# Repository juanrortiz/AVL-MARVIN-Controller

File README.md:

# MARVIN Embedded Controller — Electronics Hardware Design

**CPP AVL | Fall Cohort 2026 | Intelligent Ground Vehicle Competition (IGVC)**

This repository contains the hardware design files and embedded firmware source for a custom controller developed for **MARVIN**, the CPP Autonomous Vehicle Lab (AVL) competition platform.

The controller is built around the **STM32F767ZIT6** microcontroller and is intended to modernize MARVIN's motor-control electronics, replacing the existing **Teensy 4.1**-based controller with an STM32-based system.

## Project Goals

During the Fall 2026 cohort, the Electronics Hardware Design Team aims to:

- Design and integrate a new STM32-based embedded control system for MARVIN.
- Migrate CAN-based motor control from the existing Teensy 4.1 controller.
- Support the currently used **SPARK MAX** motor drivers over CAN.
- Improve compatibility with future **ODrive S Series** CAN motor drivers.
- Standardize the control hardware around an industry-common STM32 platform.
- Validate reliable communication, power monitoring, and operation on the vehicle.

## Hardware Overview

The custom controller integrates the following components and subsystems:

| Subsystem | Description |
| --- | --- |
| Main MCU | STM32F767ZIT6 |
| CAN Interface | CAN transceiver for communication with motor drivers |
| USB / Serial | Serial-to-USB interface for communication and debugging |
| Power Monitoring | Onboard power-monitoring circuitry |
| PCB Design | KiCad schematic and PCB layout files |

> **Note:** Electrical specifications, connector pinouts, CAN configuration, and power limits should be verified against the latest KiCad design before hardware is assembled or connected.

## Repository Contents

This repository includes:

- **KiCad project files** — schematics, PCB layouts, and related hardware design assets.
- **Firmware source code** — embedded application code targeting the STM32F767ZIT6.
- **Makefile** — firmware build configuration.
- **Linker scripts** — memory layout and linking configuration for the STM32 target.

The exact directory layout may evolve as the project develops.

## Firmware Dependencies

The firmware depends on official **STMicroelectronics STM32 HAL and CMSIS libraries**. These libraries are **not necessarily bundled with this repository** and must be obtained separately from the official STM32 software packages.

Recommended sources:

- [STM32CubeF7 firmware package](https://github.com/STMicroelectronics/STM32CubeF7)
- [STM32F7 HAL drivers](https://github.com/STMicroelectronics/stm32f7xx-hal-driver)
- [STM32Cube ecosystem](https://www.st.com/en/embedded-software/stm32cube-mcu-mpu-packages.html)

Ensure the HAL, CMSIS, startup files, include paths, and linker configuration match the **STM32F767ZIT6** and the project's Makefile. Dependency setup and build commands will be documented as the firmware structure is finalized.

## Development Roadmap

- [ ] Finalize and review the KiCad schematic and PCB design.
- [ ] Assemble and bring up the STM32F767ZIT6 controller hardware.
- [ ] Configure the clock tree, GPIO, CAN, serial/USB, and power-monitoring peripherals.
- [ ] Integrate official STM32 HAL/CMSIS dependencies into the firmware build.
- [ ] Implement and validate CAN communication with SPARK MAX motor drivers.
- [ ] Migrate motor-control functionality from Teensy 4.1 to STM32.
- [ ] Evaluate and implement compatibility with ODrive S Series CAN motor drivers.
- [ ] Perform bench testing, vehicle integration, and system validation.

*Checklist items represent project objectives, not confirmed implementation status.*

## Development and Testing Notes

Before connecting motor drivers or installing the controller on MARVIN:

1. Verify PCB power rails, grounding, and connector pinouts.
2. Confirm CAN bus voltage levels, termination, bitrate, and device-specific message protocols.
3. Test communication and power monitoring on the bench before enabling motor outputs.
4. Validate fault handling and emergency-stop behavior as part of vehicle integration.

**Important:** SPARK MAX and ODrive motor controllers may use different CAN protocols. Electrical CAN compatibility alone does not guarantee firmware-level interoperability; each device requires the appropriate protocol implementation.

## Team

**CPP Autonomous Vehicle Lab (AVL)**  
**Fall Cohort 2026 — MARVIN Electronics Hardware Design Team**  
**Competition:** Intelligent Ground Vehicle Competition (IGVC)

## Project Status

**In development — Fall 2026 cohort.** Hardware, firmware, and integration details are subject to change as the controller is developed and validated.

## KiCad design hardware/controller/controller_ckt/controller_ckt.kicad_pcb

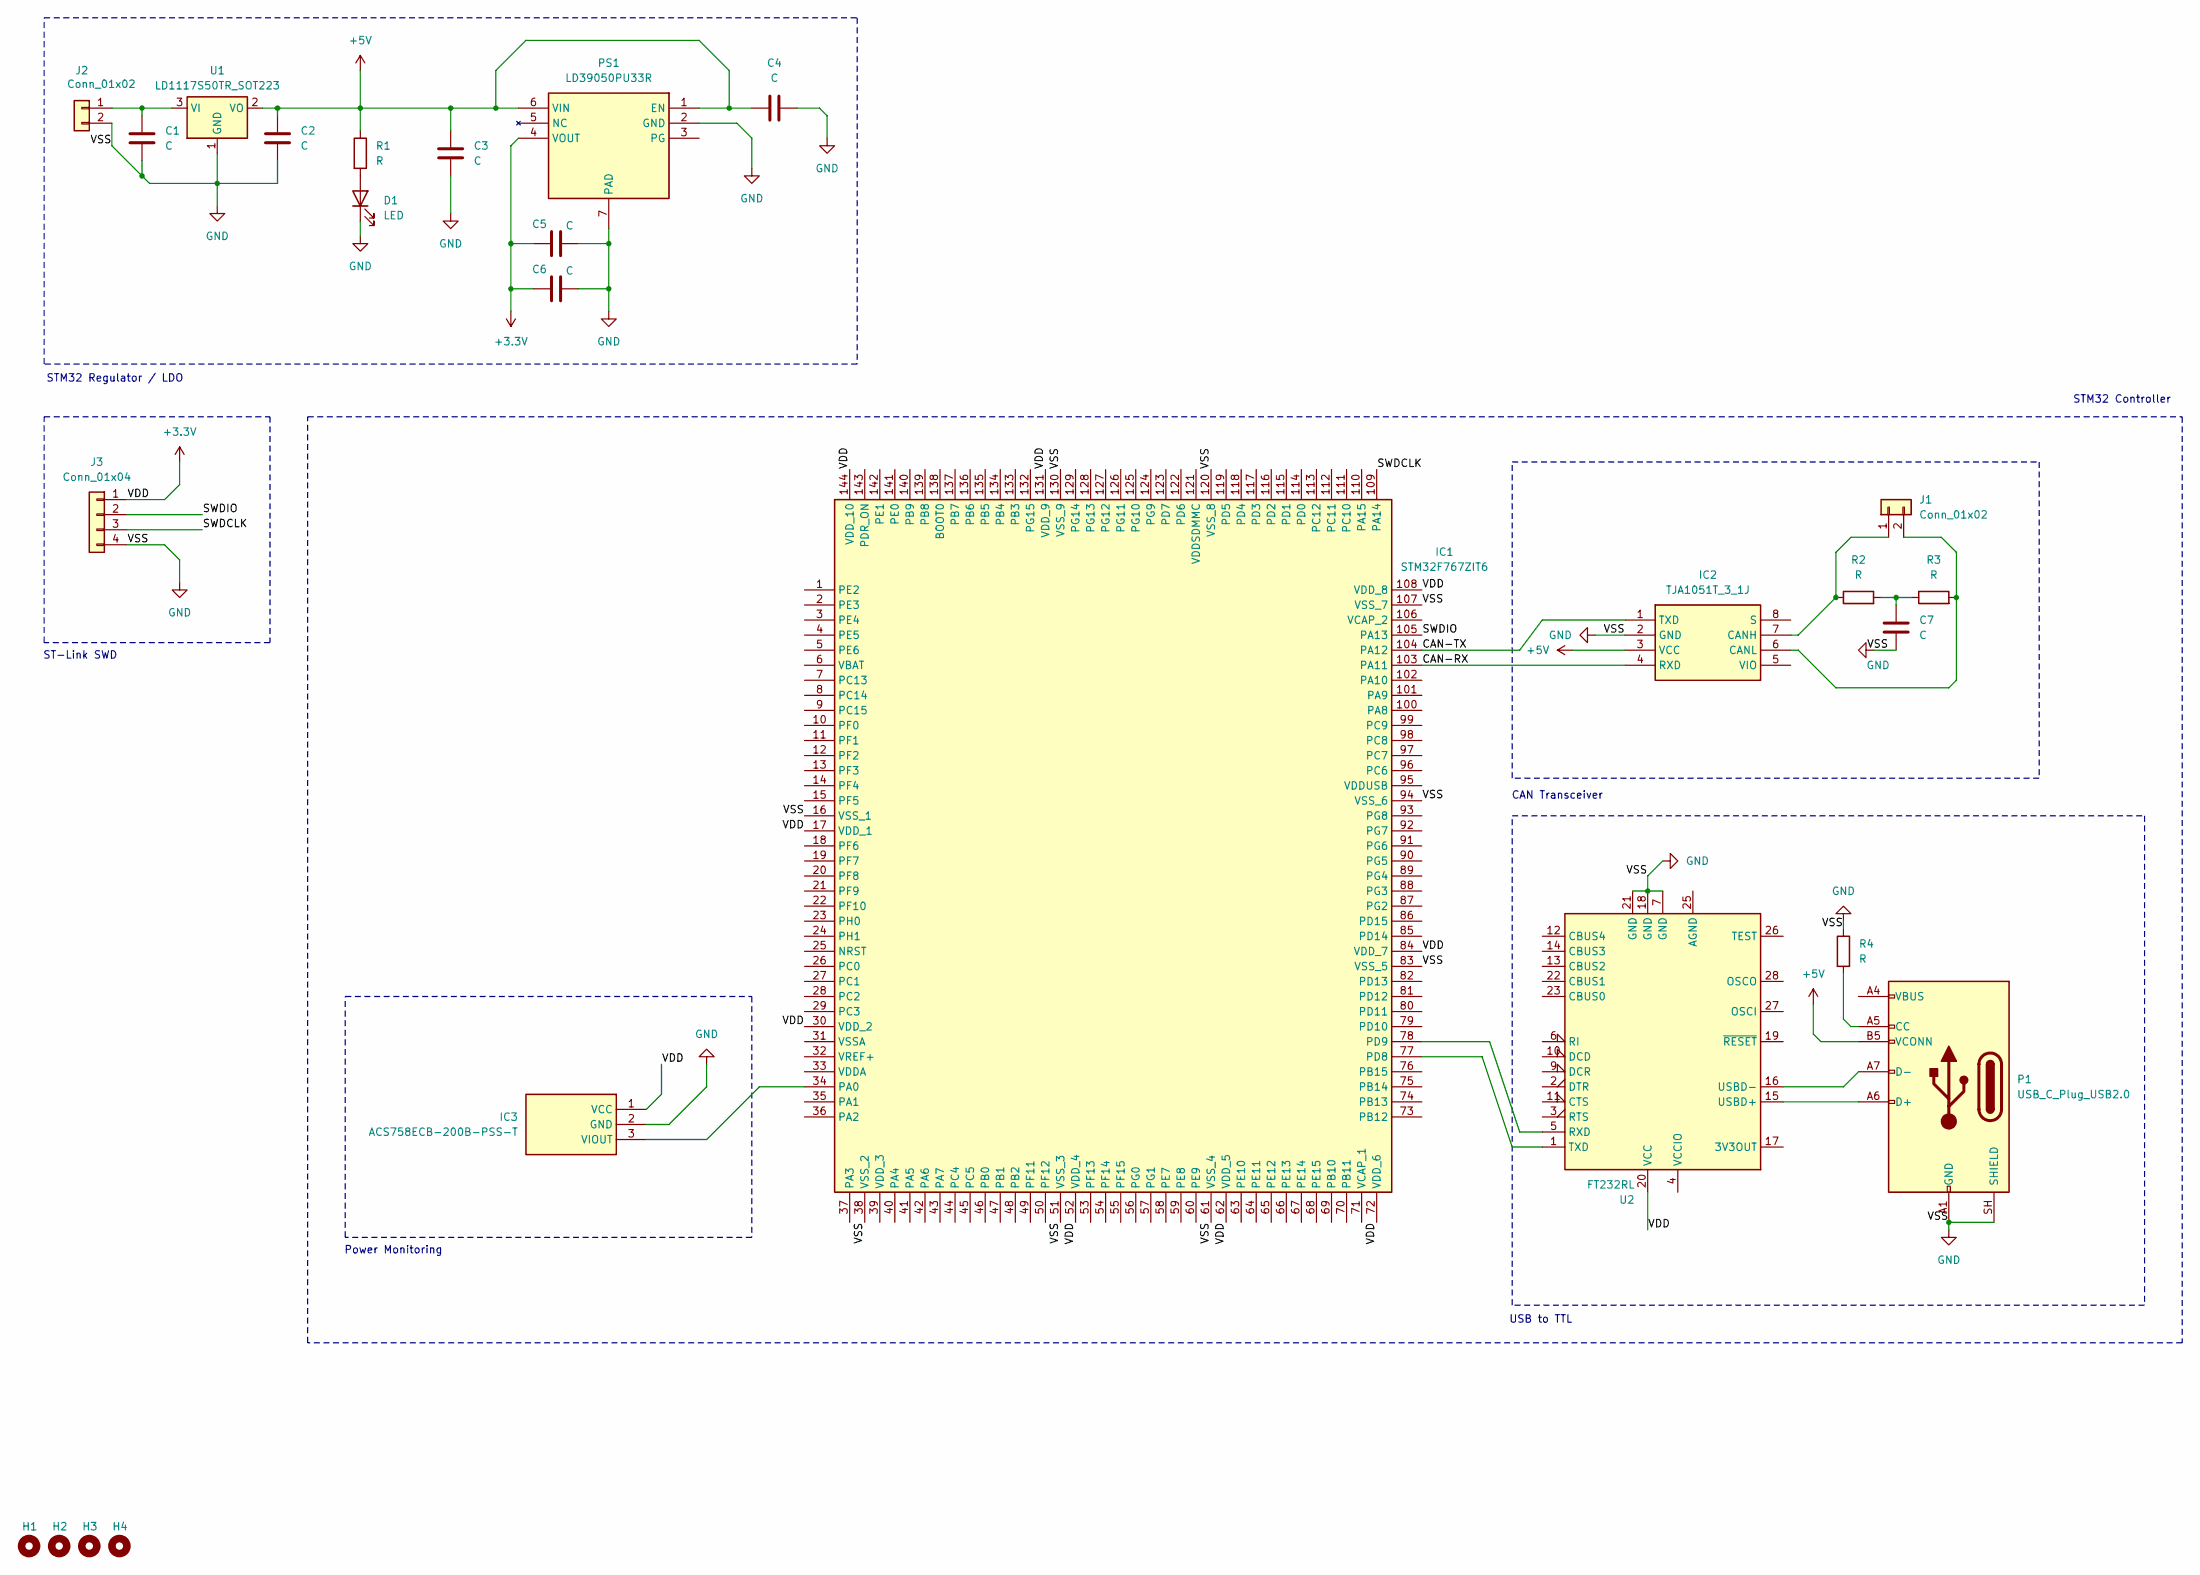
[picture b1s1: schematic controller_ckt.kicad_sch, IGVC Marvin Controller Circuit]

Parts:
C1, C2, C3, C4, C5, C6, C7: C; C_0805_2012Metric
D1: LED; LED_0805_2012Metric
H1, H2, H3, H4: MountingHole_3.2mm_M3
IC1: STM32F767ZIT6; QFP50P2200X2200X160-144N; Mouser Part Number 511-STM32F767ZIT6
IC2: TJA1051T_3_1J; SOIC127P600X175-8N; Mouser Part Number 771-TJA1051T/3/1J
IC3: ACS758ECB-200B-PSS-T; ACS758ECB200BPSST; Mouser Part Number 250-758ECB200BPSST
J1, J2: Conn_01x02; TerminalBlock_Phoenix_MKDS-3-2-5.08_1x02_P5.08mm_Horizontal
J3: Conn_01x04; PinHeader_1x04_P2.54mm_Vertical
P1: USB_C_Plug_USB2.0; USB_C_Receptacle_HCTL_HC-TYPE-C-16P-01A
PS1: LD39050PU33R; SON95P300X300X100-7N-D; Mouser Part Number 511-LD39050PU33R
R1, R2, R3, R4: R; R_0805_2012Metric
U1: LD1117S50TR_SOT223; SOT-223-3_TabPin2
U2: FT232RL; SSOP-28_5.3x10.2mm_P0.65mm

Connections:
+3.3V: C5.1, C6.1, IC1.17 (VDD_1), IC1.30 (VDD_2), IC1.52 (VDD_4), IC1.62 (VDD_5), IC1.72 (VDD_6), IC1.84 (VDD_7), IC1.108 (VDD_8), IC1.131 (VDD_9), IC1.144 (VDD_10), IC3.1 (VCC), J3.1, PS1.4 (VOUT), U2.20 (VCC)
+5V: C2.1, C3.1, C4.1, IC2.3 (VCC), P1.B5 (VCONN), PS1.1 (EN), PS1.6 (VIN), R1.1, U1.2 (VO)
/CAN-RX: IC1.103 (PA11), IC2.4 (RXD)
/CAN-TX: IC1.104 (PA12), IC2.1 (TXD)
/SWDCLK: IC1.109 (PA14), J3.3
/SWDIO: IC1.105 (PA13), J3.2
GND: C1.2, C2.2, C3.2, C4.2, C5.2, C6.2, C7.2, D1.1 (K), IC1.16 (VSS_1), IC1.38 (VSS_2), IC1.51 (VSS_3), IC1.61 (VSS_4), IC1.83 (VSS_5), IC1.94 (VSS_6), IC1.107 (VSS_7), IC1.120 (VSS_8), IC1.130 (VSS_9), IC2.2 (GND), IC3.2 (GND), J2.2, J3.4, P1.A1 (GND), P1.A12 (GND), P1.B1 (GND), P1.B12 (GND), P1.SH (SHIELD), PS1.2 (GND), PS1.7 (PAD), R4.1, U1.1 (GND), U2.7 (GND), U2.18 (GND), U2.21 (GND)
unnamed: C7.1, R2.2, R3.1
unnamed: D1.2 (A), R1.2
unnamed: IC1.34 (PA0), IC3.3 (VIOUT)
unnamed: IC1.77 (PD8), U2.1 (TXD)
unnamed: IC1.78 (PD9), U2.5 (RXD)
unnamed: IC2.7 (CANH), J1.1, R2.1
unnamed: IC2.6 (CANL), J1.2, R3.2
unnamed: C1.1, J2.1, U1.3 (VI)
unnamed: P1.A5 (CC), R4.2
unnamed: P1.A6 (D+), U2.15 (USBD+)
unnamed: P1.A7 (D-), U2.16 (USBD-)
unnamed: P1.A4 (VBUS), P1.A9 (VBUS), P1.B4 (VBUS), P1.B9 (VBUS)

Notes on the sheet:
STM32 Regulator / LDO
USB to TTL
Power Monitoring
STM32 Controller
ST-Link SWD
CAN Transceiver

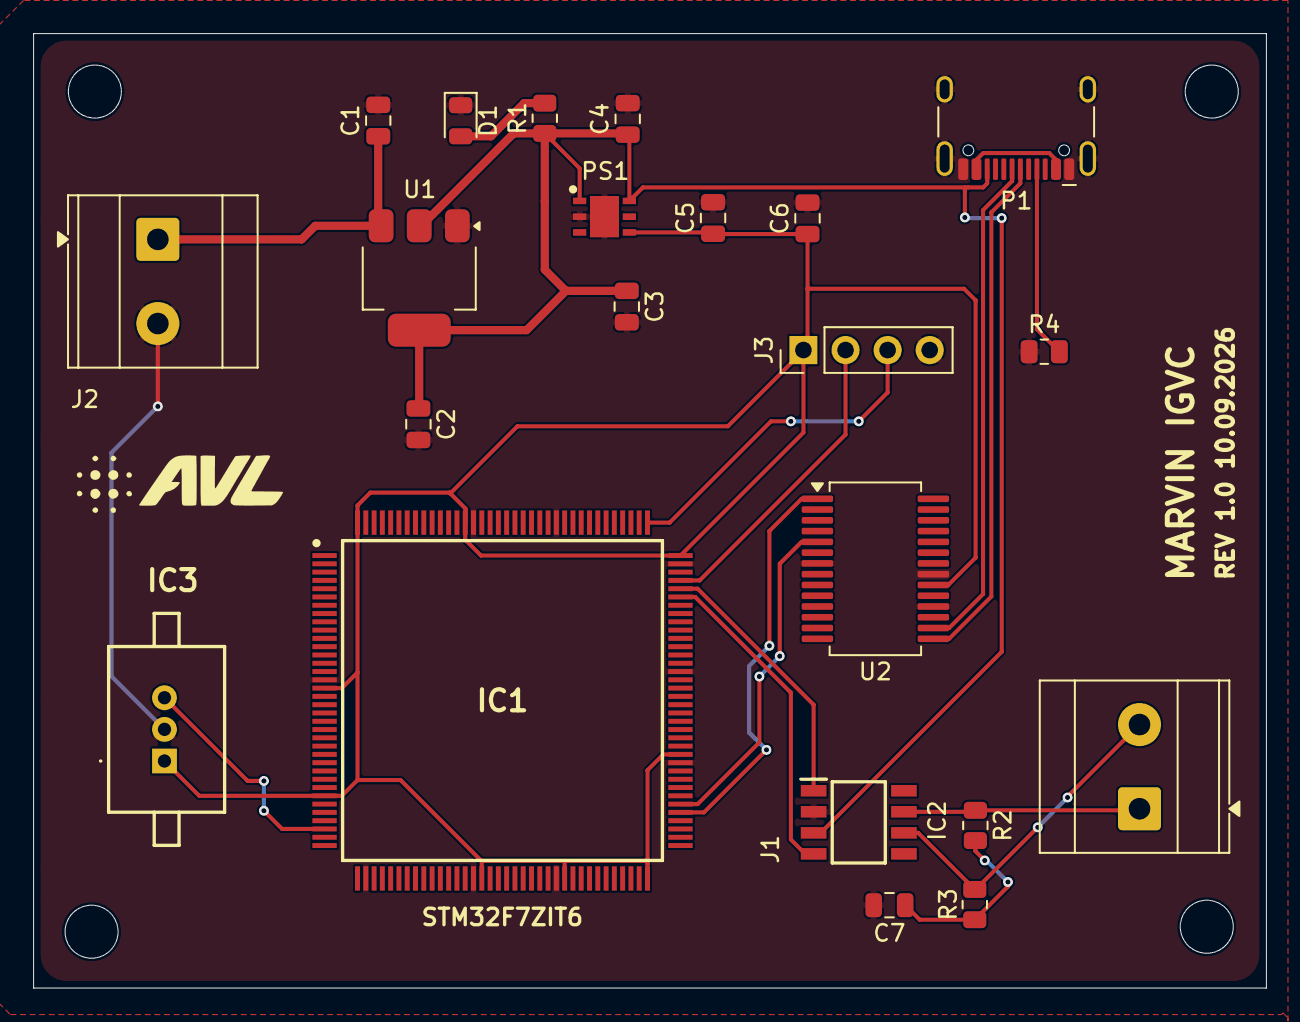
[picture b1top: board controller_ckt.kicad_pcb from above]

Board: 2 copper layers, 74.4 x 57.6 mm, 26 parts (0 on the bottom side), 19 nets.
